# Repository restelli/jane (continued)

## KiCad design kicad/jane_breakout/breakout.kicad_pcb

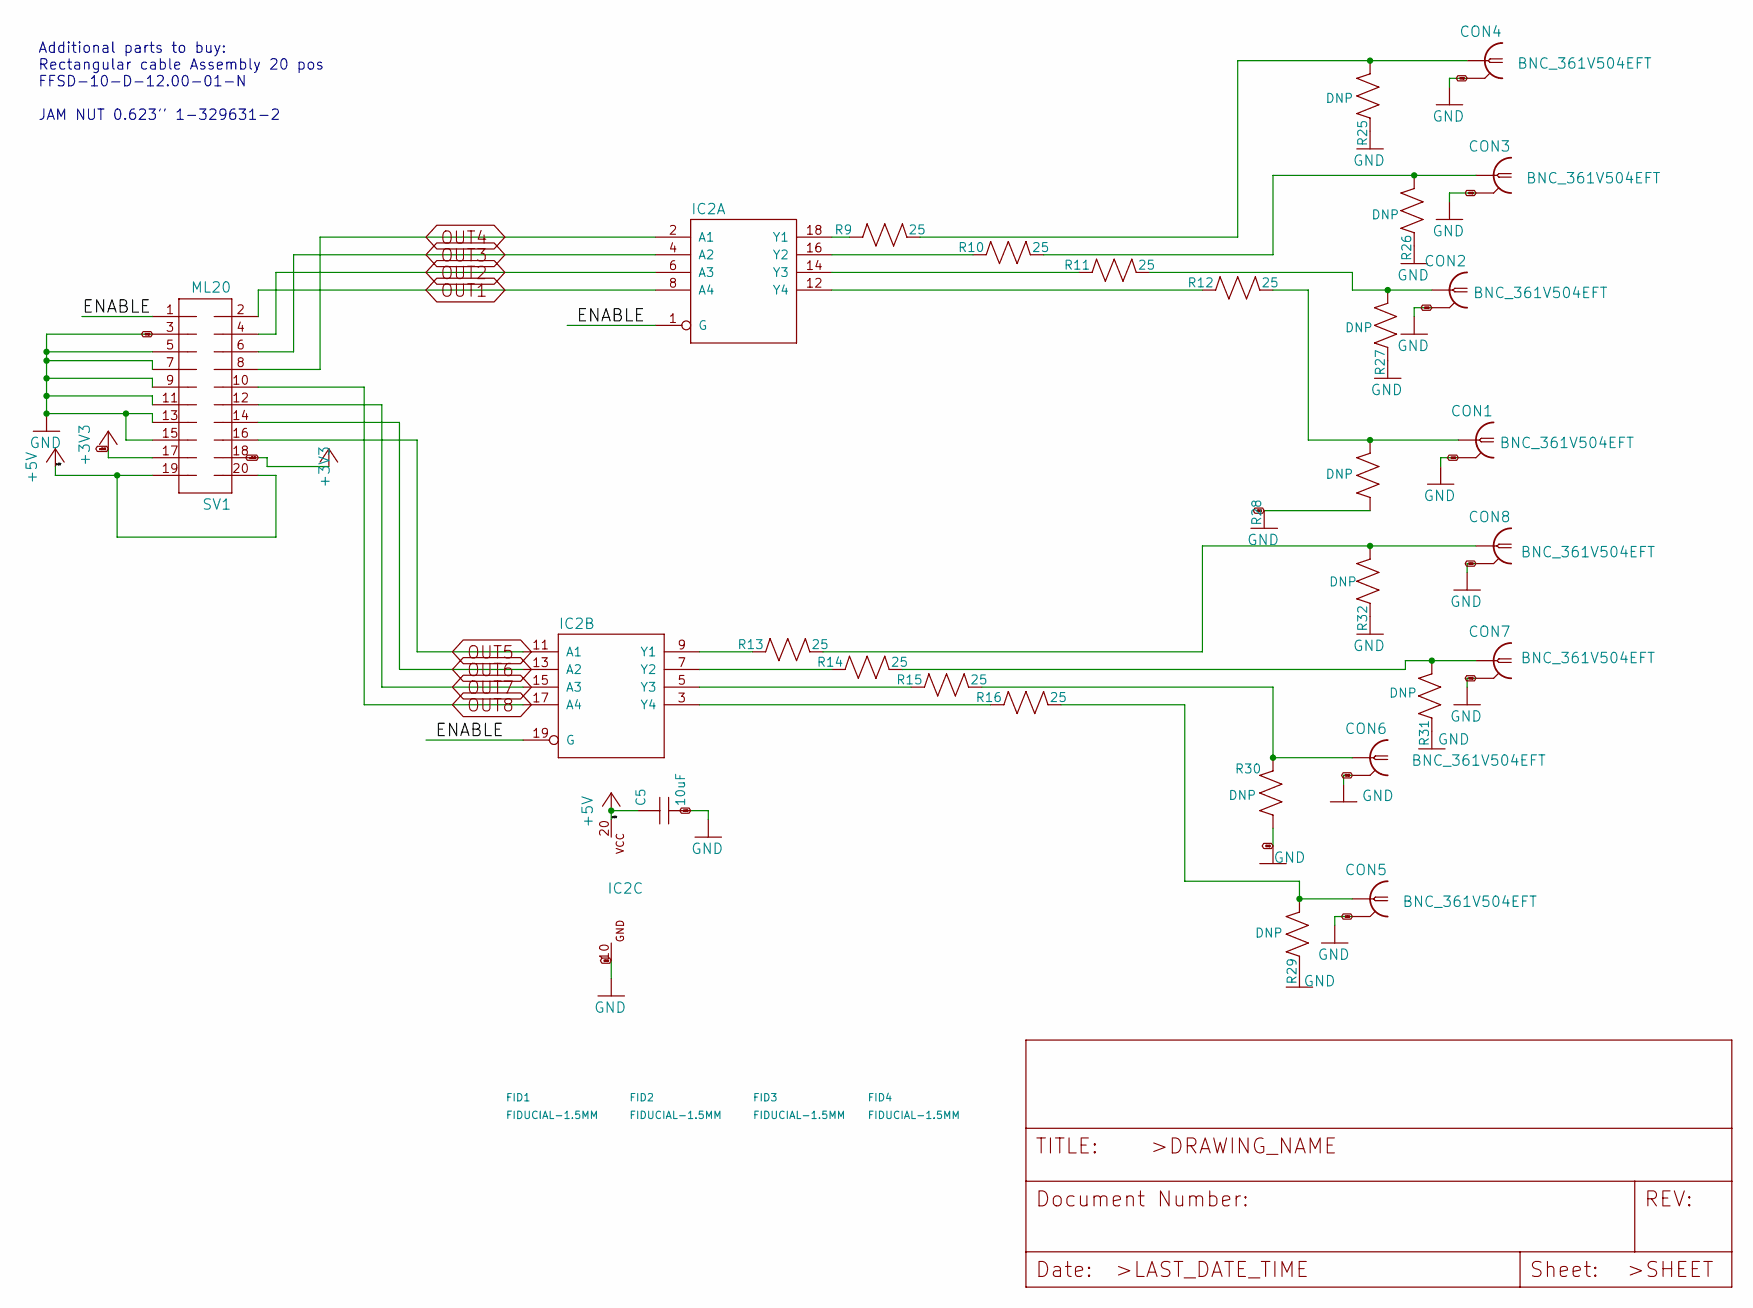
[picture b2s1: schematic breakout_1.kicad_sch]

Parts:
C5: 10uF; C_MLCC_0603; PARTNO C3225X5R1E106K250AA
CON1, CON2, CON3, CON4, CON5, CON6, CON7, CON8: BNC_361V504EFT; BNC_V-BITE_PCB_EDGE; PARTNO 361V504EFT
FID1, FID2, FID3, FID4: FIDUCIAL-1.5MM; FID_1.5MM
IC2: 74244DW; SO20W; PARTNO SN74S244DWR
R9, R10, R11, R12, R13, R14, R15, R16: 25; R_0603; PARTNO RK73H1JTTD24R9F
R25, R26, R27, R28, R29, R30, R31, R32: DNP; R_0603
SV1: ML20; PARTNO 302-S201

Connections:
+3V3: SV1.17, SV1.18; also elsewhere on the board
+5V: C5.P$1 (1), IC2.20 (VCC), SV1.19, SV1.20
/breakout_1/ENABLE: IC2.1 (G), IC2.19 (G), SV1.1
GND: C5.P$2 (2), CON1.GND$1 (2), CON1.GND$2 (2), CON2.GND$1 (2), CON2.GND$2 (2), CON3.GND$1 (2), CON3.GND$2 (2), CON4.GND$1 (2), CON4.GND$2 (2), CON5.GND$1 (2), CON5.GND$2 (2), CON6.GND$1 (2), CON6.GND$2 (2), CON7.GND$1 (2), CON7.GND$2 (2), CON8.GND$1 (2), CON8.GND$2 (2), IC2.10 (GND), R25.P$1 (1), R26.P$1 (1), R27.P$1 (1), R28.P$1 (1), R29.P$1 (1), R30.P$1 (1), R31.P$1 (1), R32.P$1 (1), SV1.3, SV1.5, SV1.7, SV1.9, SV1.11, SV1.13, SV1.15; also elsewhere on the board
unnamed: CON1.P$1 (1), R12.P$2 (2), R28.P$2 (2)
unnamed: CON2.P$1 (1), R11.P$2 (2), R27.P$2 (2)
unnamed: CON3.P$1 (1), R10.P$2 (2), R26.P$2 (2)
unnamed: CON4.P$1 (1), R9.P$2 (2), R25.P$2 (2)
unnamed: CON5.P$1 (1), R16.P$2 (2), R29.P$2 (2)
unnamed: CON6.P$1 (1), R15.P$2 (2), R30.P$2 (2)
unnamed: CON7.P$1 (1), R14.P$2 (2), R31.P$2 (2)
unnamed: CON8.P$1 (1), R13.P$2 (2), R32.P$2 (2)
unnamed: IC2.3 (Y4), R16.P$1 (1)
unnamed: IC2.5 (Y3), R15.P$1 (1)
unnamed: IC2.7 (Y2), R14.P$1 (1)
unnamed: IC2.9 (Y1), R13.P$1 (1)
unnamed: IC2.12 (Y4), R12.P$1 (1)
unnamed: IC2.14 (Y3), R11.P$1 (1)
unnamed: IC2.16 (Y2), R10.P$1 (1)
unnamed: IC2.18 (Y1), R9.P$1 (1)
OUT1: IC2.8 (A4), SV1.2; also elsewhere on the board
OUT2: IC2.6 (A3), SV1.4; also elsewhere on the board
OUT3: IC2.4 (A2), SV1.6; also elsewhere on the board
OUT4: IC2.2 (A1), SV1.8; also elsewhere on the board
OUT5: IC2.11 (A1), SV1.16; also elsewhere on the board
OUT6: IC2.13 (A2), SV1.14; also elsewhere on the board
OUT7: IC2.15 (A3), SV1.12; also elsewhere on the board
OUT8: IC2.17 (A4), SV1.10; also elsewhere on the board

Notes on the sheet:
Additional parts to buy: Rectangular cable Assembly 20 pos FFSD-10-D-12.00-01-N JAM NUT 0.623'' 1-329631-2

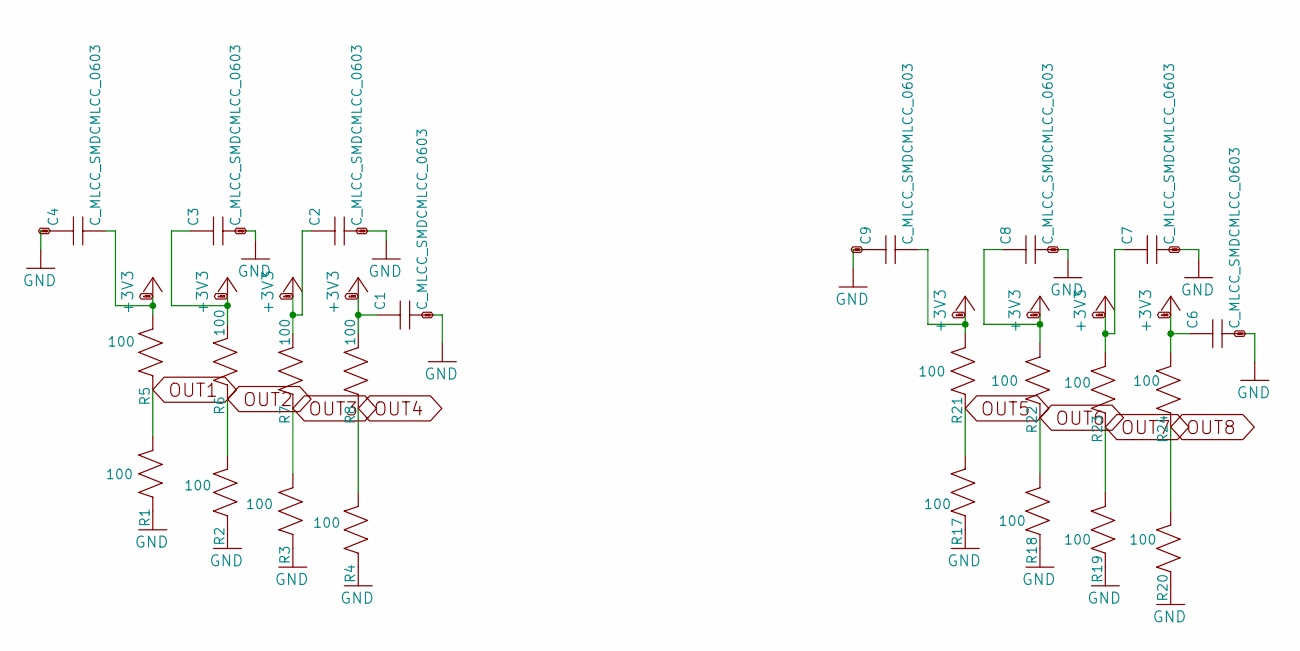
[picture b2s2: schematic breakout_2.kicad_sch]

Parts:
C1, C2, C3, C4, C6, C7, C8, C9: C_MLCC_SMDCMLCC_0603; C_MLCC_0603
R1, R2, R3, R4, R5, R6, R7, R8, R17, R18, R19, R20, R21, R22, R23, R24: 100; R_0603; PARTNO RK73H1JTTD1000F

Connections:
+3V3: C1.P$1 (1), C2.P$1 (1), C3.P$1 (1), C4.P$2 (2), C6.P$1 (1), C7.P$1 (1), C8.P$1 (1), C9.P$2 (2), R5.P$2 (2), R6.P$2 (2), R7.P$2 (2), R8.P$2 (2), R21.P$2 (2), R22.P$2 (2), R23.P$2 (2), R24.P$2 (2); also elsewhere on the board
GND: C1.P$2 (2), C2.P$2 (2), C3.P$2 (2), C4.P$1 (1), C6.P$2 (2), C7.P$2 (2), C8.P$2 (2), C9.P$1 (1), R1.P$1 (1), R2.P$1 (1), R3.P$1 (1), R4.P$1 (1), R17.P$1 (1), R18.P$1 (1), R19.P$1 (1), R20.P$1 (1); also elsewhere on the board
OUT1: R1.P$2 (2), R5.P$1 (1); also elsewhere on the board
OUT2: R2.P$2 (2), R6.P$1 (1); also elsewhere on the board
OUT3: R3.P$2 (2), R7.P$1 (1); also elsewhere on the board
OUT4: R4.P$2 (2), R8.P$1 (1); also elsewhere on the board
OUT5: R17.P$2 (2), R21.P$1 (1); also elsewhere on the board
OUT6: R18.P$2 (2), R22.P$1 (1); also elsewhere on the board
OUT7: R19.P$2 (2), R23.P$1 (1); also elsewhere on the board
OUT8: R20.P$2 (2), R24.P$1 (1); also elsewhere on the board

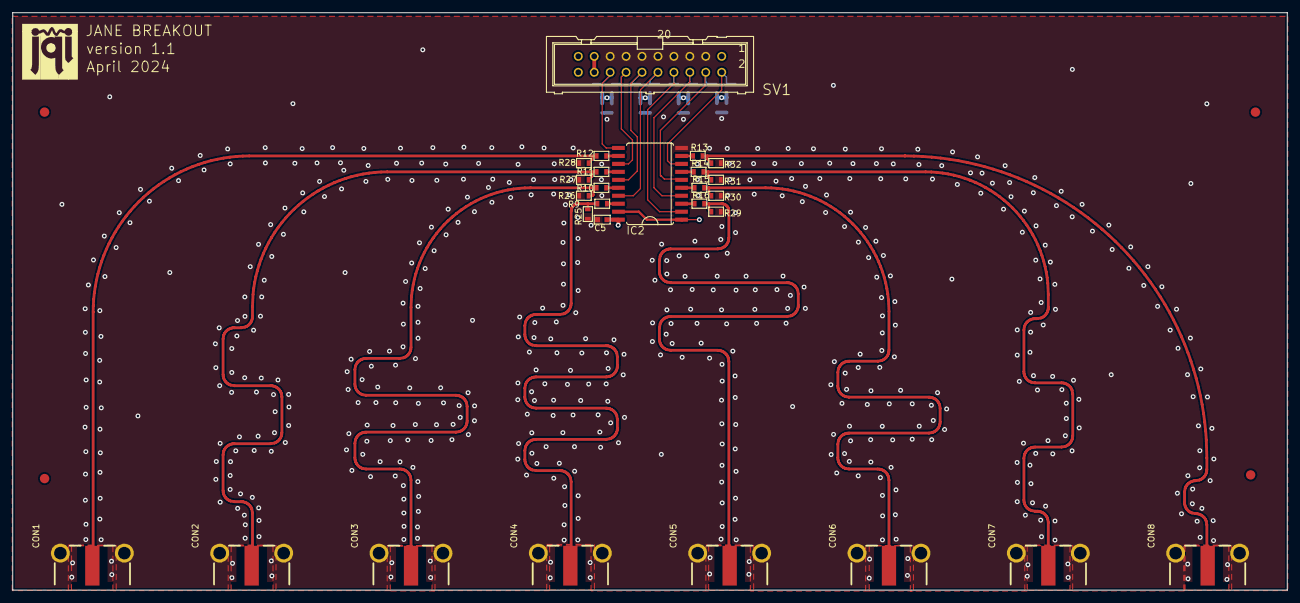
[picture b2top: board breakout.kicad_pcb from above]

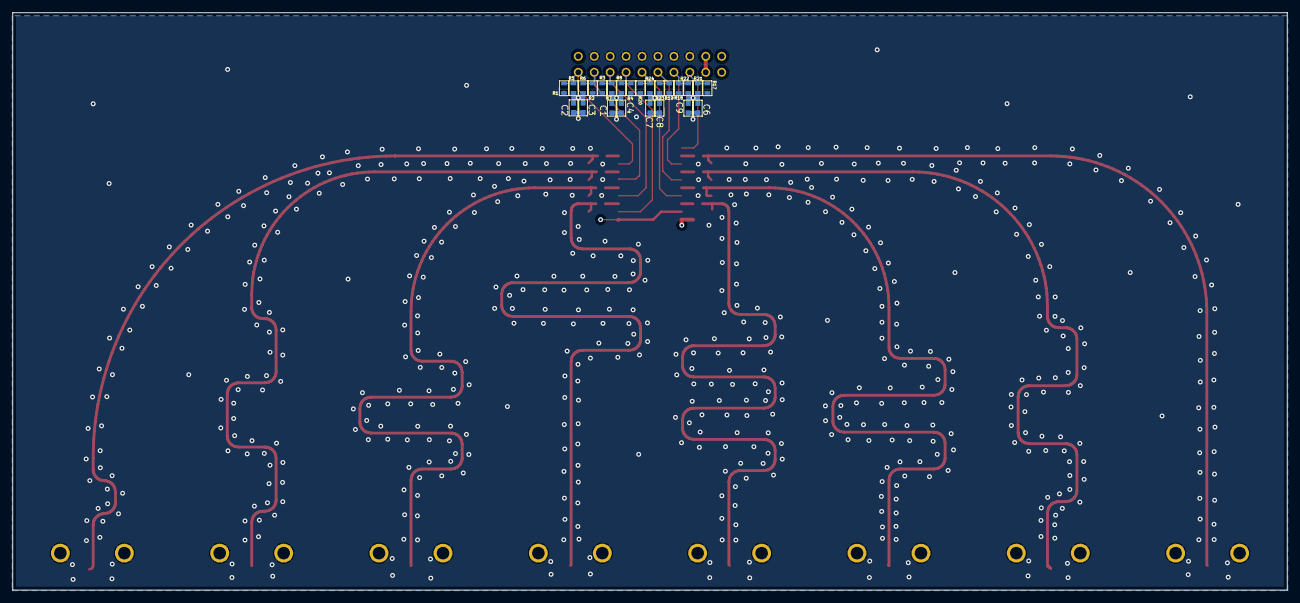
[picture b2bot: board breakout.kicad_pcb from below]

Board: 4 copper layers, 203.2 x 92.0 mm, 56 parts (24 on the bottom side), 28 nets.

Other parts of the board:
LOGO1: JQI-LOGOSILK; JQI_LOGO_NEGATIVE-SILKSCREEN

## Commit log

2024-04-30 Retouches to the silkscreen
    Migrated to version 8 of Kicad.
    gerber were generated and sent to fabrication.
    Unfortunately the PCB file were overwritten before commiting, so the
    current touches to the silkscreen are not isentical to the ones
    submitted.
